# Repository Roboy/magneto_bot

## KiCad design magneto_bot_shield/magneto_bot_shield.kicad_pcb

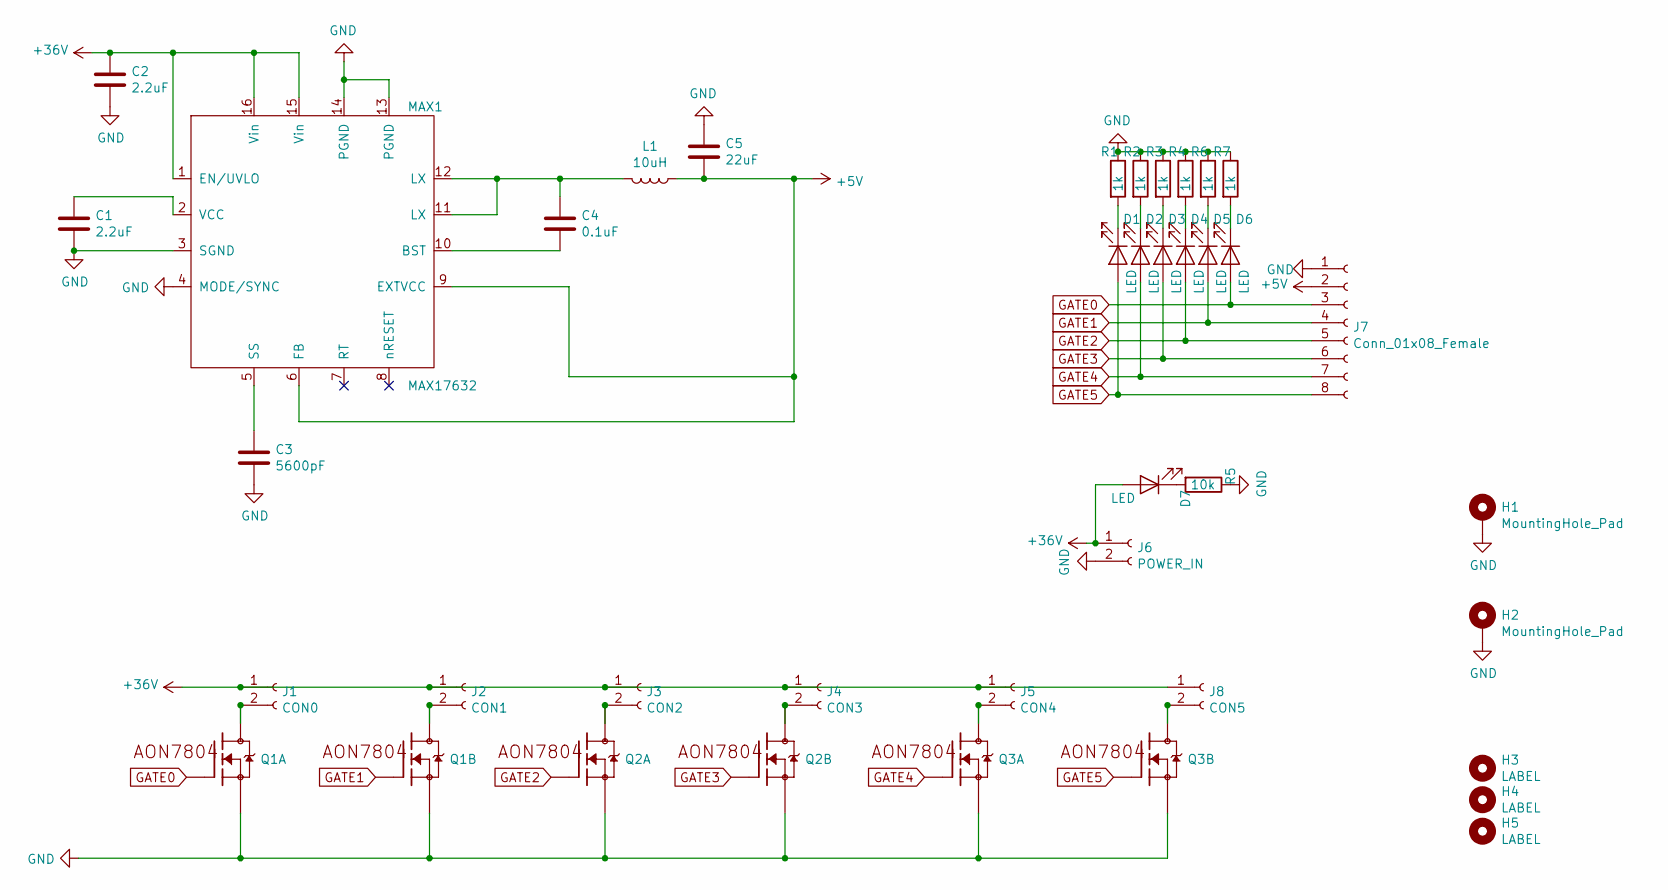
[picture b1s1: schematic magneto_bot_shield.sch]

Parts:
C1, C2: 2.2uF; C_0402_1005Metric
C3: 5600pF; C_0402_1005Metric
C4: 0.1uF; C_0402_1005Metric
C5: 22uF; C_0805_2012Metric
D1, D2, D3, D4, D5, D6, D7: LED; LED_0402_1005Metric
H1, H2: MountingHole_Pad; MountingHole_2.2mm_M2_Pad
H3: LABEL; R1_ear_silk_5.5mm
H4: LABEL; R1_eyes_mask_5.5mm
H5: LABEL; R1_face_mask_5.5mm
J1: CON0; Wago_2060_2_SMD
J2: CON1; Wago_2060_2_SMD
J3: CON2; Wago_2060_2_SMD
J4: CON3; Wago_2060_2_SMD
J5: CON4; Wago_2060_2_SMD
J6: POWER_IN; Wago_2060_2_SMD
J7: Conn_01x08_Female; micro_match_female_8pos_SMT
J8: CON5; Wago_2060_2_SMD
L1: 10uH; XAL5050-103MEC
MAX1: MAX17632; QFN-16-1EP_3x3mm_Pitch0.5mm
Q1, Q2, Q3: AON7804; DFN3X3
R1, R2, R3, R4, R6, R7: 1k; R_0402_1005Metric
R5: 10k; R_0402_1005Metric

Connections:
+5V: C5.2, J7.2, L1.1, MAX1.6 (FB), MAX1.9 (EXTVCC)
+36V: C2.1, D7.2 (A), J1.1, J2.1, J3.1, J4.1, J5.1, J6.1, J8.1, MAX1.1 (EN/UVLO), MAX1.15 (Vin), MAX1.16 (Vin)
GATE0: D6.2 (A), J7.3, Q1.G1 (G)
GATE1: D5.2 (A), J7.4, Q1.G2 (G)
GATE2: D4.2 (A), J7.5, Q2.G1 (G)
GATE3: D3.2 (A), J7.6, Q2.G2 (G)
GATE4: D2.2 (A), J7.7, Q3.G1 (G)
GATE5: D1.2 (A), J7.8, Q3.G2 (G)
GND: C1.2, C2.2, C3.2, C5.1, H1.1, H2.1, J6.2, J7.1, MAX1.3 (SGND), MAX1.4 (MODE/SYNC), MAX1.13 (PGND), MAX1.14 (PGND), Q1.S1 (S), Q1.S2 (S), Q2.S1 (S), Q2.S2 (S), Q3.S1 (S), Q3.S2 (S), R1.1, R2.1, R3.1, R4.1, R5.1, R6.1, R7.1
unnamed: C1.1, MAX1.2 (VCC)
unnamed: C3.1, MAX1.5 (SS)
unnamed: C4.1, L1.2, MAX1.11 (LX), MAX1.12 (LX)
unnamed: C4.2, MAX1.10 (BST)
unnamed: D1.1 (K), R1.2
unnamed: D2.1 (K), R2.2
unnamed: D3.1 (K), R3.2
unnamed: D4.1 (K), R4.2
unnamed: D5.1 (K), R6.2
unnamed: D6.1 (K), R7.2
unnamed: D7.1 (K), R5.2
unnamed: J1.2, Q1.D1 (D), Q1.D1A (D1)
unnamed: J2.2, Q1.D2 (D), Q1.D2A (D1)
unnamed: J3.2, Q2.D1 (D), Q2.D1A (D1)
unnamed: J4.2, Q2.D2 (D), Q2.D2A (D1)
unnamed: J5.2, Q3.D1 (D), Q3.D1A (D1)
unnamed: J8.2, Q3.D2 (D), Q3.D2A (D1)

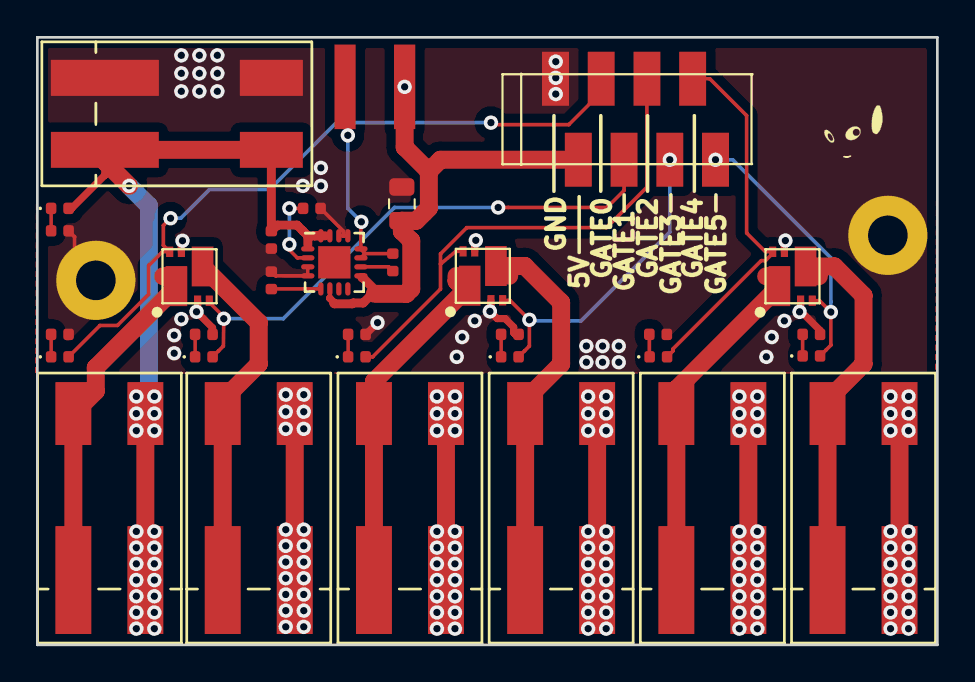
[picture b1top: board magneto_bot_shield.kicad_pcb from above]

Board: 2 copper layers, 50.0 x 33.7 mm, 37 parts (0 on the bottom side), 26 nets.

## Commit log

2019-12-04 draft
2019-12-06 primitive servo sweep
2020-03-12 fixed wrong gate-source arrangement
